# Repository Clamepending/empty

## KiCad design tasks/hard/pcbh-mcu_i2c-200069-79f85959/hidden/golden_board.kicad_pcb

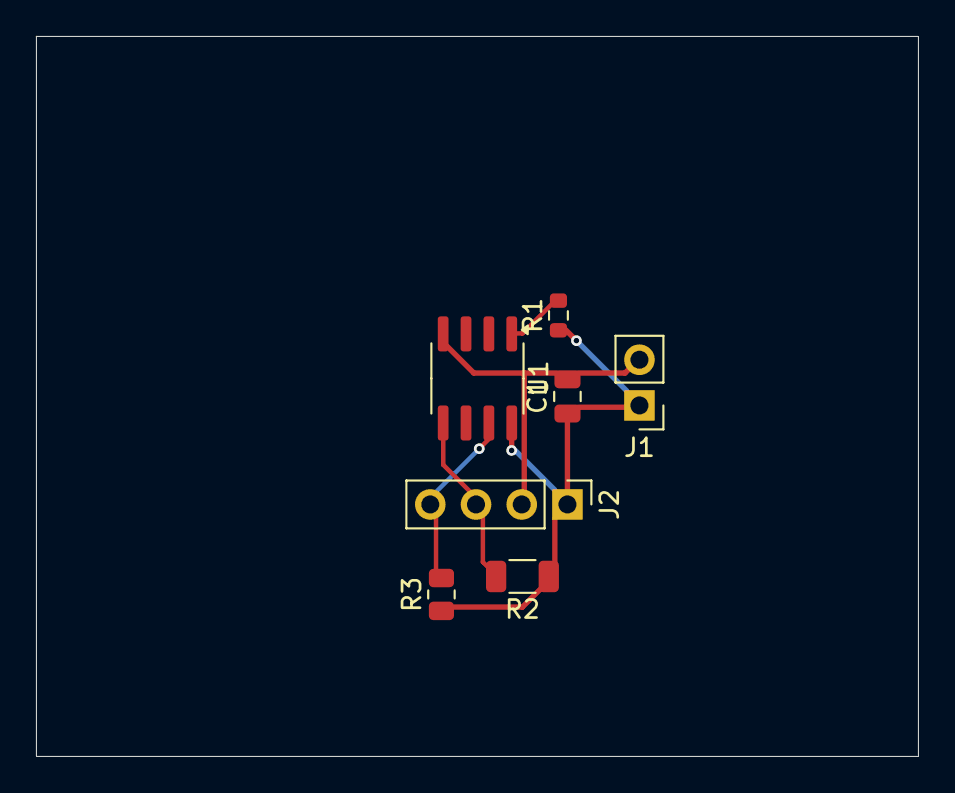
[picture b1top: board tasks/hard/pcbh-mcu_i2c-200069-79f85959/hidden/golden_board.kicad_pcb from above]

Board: 2 copper layers, 49.0 x 40.0 mm, 7 parts (0 on the bottom side), 5 nets.

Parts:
C1: 100n; C_0805_2012Metric
J1: PinHeader_1x02_P2.54mm_Vertical
J2: PinHeader_1x04_P2.54mm_Vertical
R1: 8.2k; R_0603_1608Metric
R2: 3k; R_1206_3216Metric
R3: 3k; R_0805_2012Metric
U1: SOIC-8_3.9x4.9mm_P1.27mm

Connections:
+5V: C1.1, J1.1, J2.1, R1.1, R2.1, R3.1, U1.8
GND: C1.2, J1.2, J2.2, U1.4
NRST: R1.2, U1.1
SCL: J2.4, R3.2, U1.7
SDA: J2.3, R2.2, U1.5

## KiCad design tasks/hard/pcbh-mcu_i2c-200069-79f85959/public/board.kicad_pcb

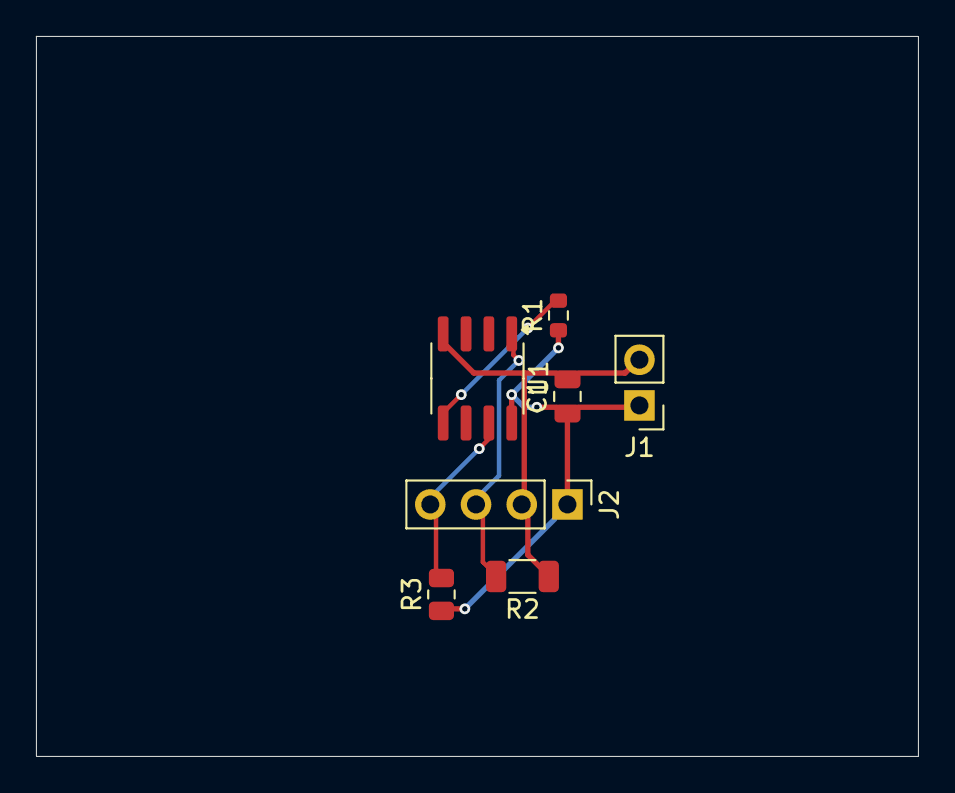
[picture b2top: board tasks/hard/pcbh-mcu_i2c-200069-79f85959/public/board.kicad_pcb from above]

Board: 2 copper layers, 49.0 x 40.0 mm, 7 parts (0 on the bottom side), 5 nets.

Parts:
C1: 100n; C_0805_2012Metric
J1: PinHeader_1x02_P2.54mm_Vertical
J2: PinHeader_1x04_P2.54mm_Vertical
R1: 8.2k; R_0603_1608Metric
R2: 3k; R_1206_3216Metric
R3: 3k; R_0805_2012Metric
U1: SOIC-8_3.9x4.9mm_P1.27mm

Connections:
+5V: C1.1, J1.1, J2.1, R1.1, R3.1, U1.8
GND: C1.2, J1.2, J2.2, R2.1, U1.4
NRST: R1.2, U1.5
SCL: J2.4, R3.2, U1.7
SDA: J2.3, R2.2, U1.1

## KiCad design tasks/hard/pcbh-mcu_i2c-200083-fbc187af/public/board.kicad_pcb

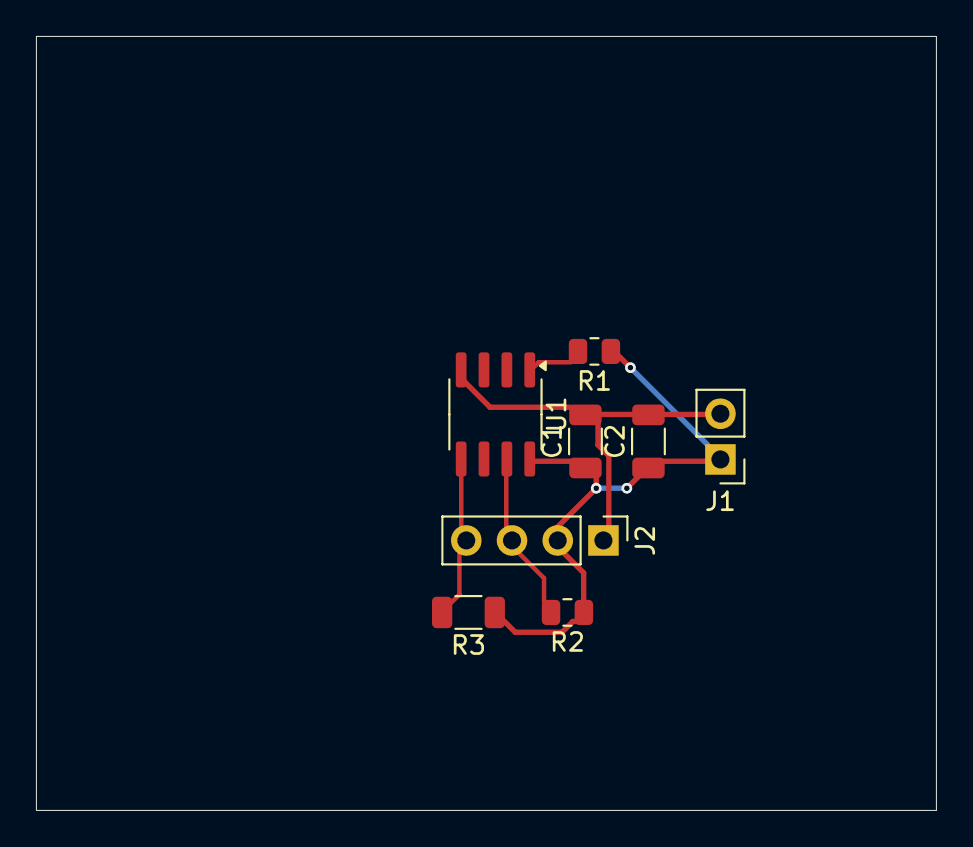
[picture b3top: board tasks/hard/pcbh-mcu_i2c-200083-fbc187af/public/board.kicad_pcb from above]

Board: 2 copper layers, 50.0 x 43.0 mm, 8 parts (0 on the bottom side), 5 nets.

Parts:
C1, C2: 4.7u; C_1206_3216Metric
J1: PinHeader_1x02_P2.54mm_Vertical
J2: PinHeader_1x04_P2.54mm_Vertical
R1: 36k; R_0805_2012Metric
R2: 47k; R_0805_2012Metric
R3: 4.3k; R_1206_3216Metric
U1: SOIC-8_3.9x4.9mm_P1.27mm

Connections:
+2V5: C1.1, C2.1, J1.1, J2.2, R1.1, R2.1, R3.1, U1.8
GND: C1.2, C2.2, J1.2, J2.1, U1.4
NRST: R1.2, U1.1
SCL: J2.4, R3.2, U1.5
SDA: J2.3, R2.2, U1.7

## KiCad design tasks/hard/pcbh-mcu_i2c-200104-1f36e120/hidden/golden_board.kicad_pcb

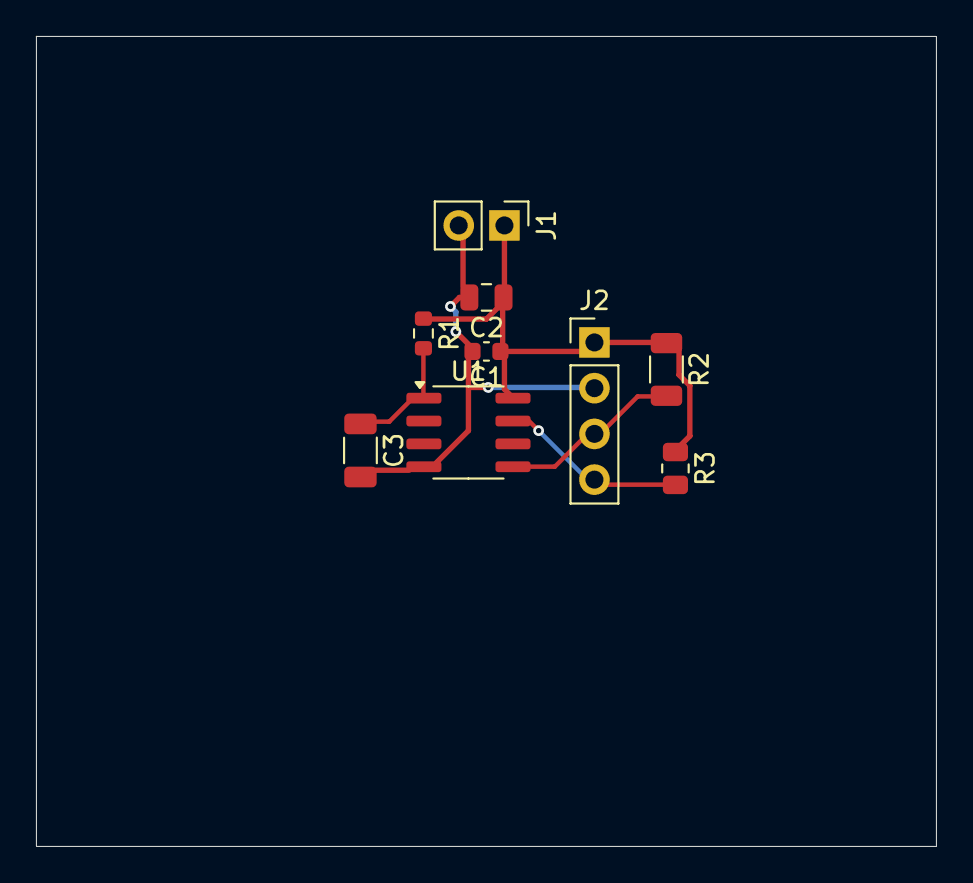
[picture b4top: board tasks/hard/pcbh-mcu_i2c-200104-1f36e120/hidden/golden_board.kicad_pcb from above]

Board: 2 copper layers, 50.0 x 45.0 mm, 9 parts (0 on the bottom side), 5 nets.

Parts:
C1: 100n; C_0603_1608Metric
C2: 1u; C_0805_2012Metric
C3: 100n; C_1206_3216Metric
J1: PinHeader_1x02_P2.54mm_Vertical
J2: PinHeader_1x04_P2.54mm_Vertical
R1: 10k; R_0603_1608Metric
R2: 4.7k; R_1206_3216Metric
R3: 4.7k; R_0805_2012Metric
U1: SOIC-8_3.9x4.9mm_P1.27mm

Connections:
+2V5: C1.1, C2.1, J1.1, J2.1, R1.1, R2.1, R3.1, U1.8
GND: C1.2, C2.2, C3.2, J1.2, J2.2, U1.4
NRST: C3.1, R1.2, U1.1
SCL: J2.4, R3.2, U1.7
SDA: J2.3, R2.2, U1.5
